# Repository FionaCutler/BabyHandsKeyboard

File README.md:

# Baby Hands Keyboard
A keyboard for those with smaller hands, layout designed by Brooke. Layout:

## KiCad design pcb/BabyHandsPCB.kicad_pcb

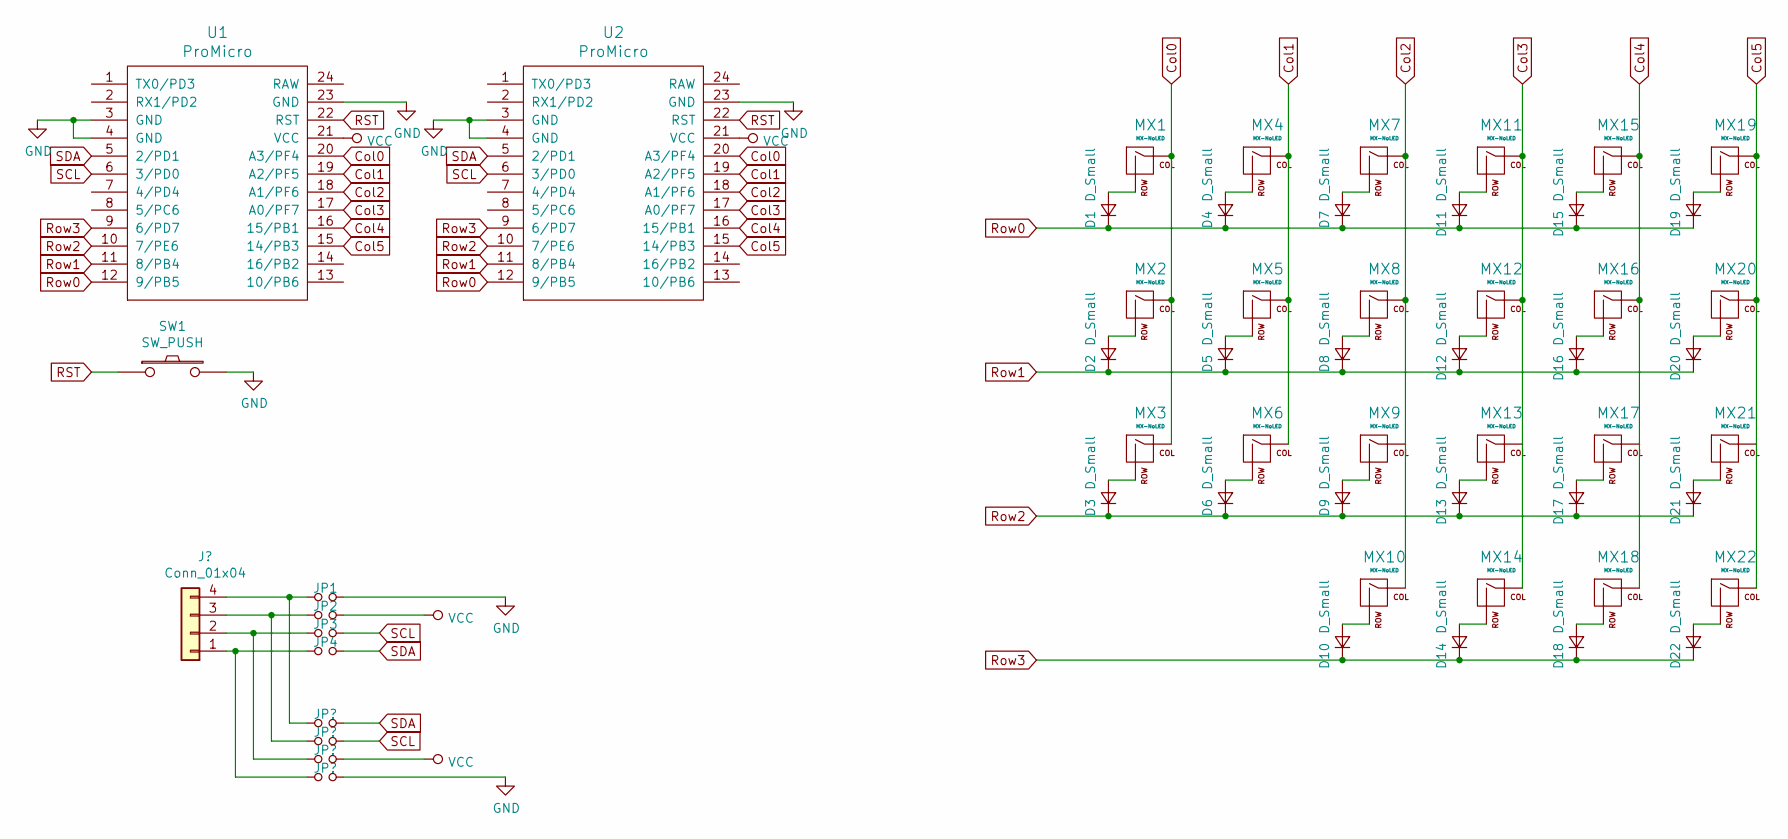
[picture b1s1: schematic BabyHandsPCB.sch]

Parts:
D1, D2, D3, D4, D5, D6, D7, D8, D9, D10, D11, D12, D13, D14, D15, D16, D17, D18, D19, D20, D21, D22: D_Small; D3_TH_SMD
JP1, JP2, JP3, JP4: Jumper_NO_Small; Jumper
MX1, MX2, MX3, MX4, MX5, MX6, MX7, MX8, MX9, MX10, MX11, MX12, MX13, MX14, MX15, MX16, MX17, MX19, MX20, MX21: MX-NoLED; CherryMX_Choc_Hotswap
MX18, MX22: MX-NoLED; CherryMX_Choc_Hotswap_1.5u
SW1: SW_PUSH; SW_Tactile_SPST_Angled_PTS645Vx31-2LFS
U1, U2: ProMicro; ArduinoProMicro-BackSide

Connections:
Col0: MX1.1 (COL), MX2.1 (COL), MX3.1 (COL), U1.20 (A3/PF4), U2.20 (A3/PF4)
Col1: MX4.1 (COL), MX5.1 (COL), MX6.1 (COL), U1.19 (A2/PF5), U2.19 (A2/PF5); also elsewhere on the board
Col2: MX7.1 (COL), MX8.1 (COL), MX9.1 (COL), MX10.1 (COL), U1.18 (A1/PF6), U2.18 (A1/PF6)
Col3: MX11.1 (COL), MX12.1 (COL), MX13.1 (COL), MX14.1 (COL), U1.17 (A0/PF7), U2.17 (A0/PF7)
Col4: MX15.1 (COL), MX16.1 (COL), MX17.1 (COL), MX18.1 (COL), U1.16 (15/PB1), U2.16 (15/PB1)
Col5: MX19.1 (COL), MX20.1 (COL), MX21.1 (COL), MX22.1 (COL), U1.15 (14/PB3), U2.15 (14/PB3)
GND: JP1.2, SW1.2, U1.3 (GND), U1.4 (GND), U1.23 (GND), U2.3 (GND), U2.4 (GND), U2.23 (GND); also elsewhere on the board
unnamed: D1.2 (A), MX1.2 (ROW)
unnamed: D2.2 (A), MX2.2 (ROW)
unnamed: D3.2 (A), MX3.2 (ROW)
unnamed: D4.2 (A), MX4.2 (ROW)
unnamed 11: D5.2 (A), MX5.2 (ROW); also elsewhere on the board
unnamed: D6.2 (A), MX6.2 (ROW)
unnamed: D7.2 (A), MX7.2 (ROW)
unnamed: D8.2 (A), MX8.2 (ROW)
unnamed: D9.2 (A), MX9.2 (ROW)
unnamed: D10.2 (A), MX10.2 (ROW)
unnamed: D11.2 (A), MX11.2 (ROW)
unnamed: D12.2 (A), MX12.2 (ROW)
unnamed: D13.2 (A), MX13.2 (ROW)
unnamed: D14.2 (A), MX14.2 (ROW)
unnamed: D15.2 (A), MX15.2 (ROW)
unnamed: D16.2 (A), MX16.2 (ROW)
unnamed: D17.2 (A), MX17.2 (ROW)
unnamed: D18.2 (A), MX18.2 (ROW)
unnamed: D19.2 (A), MX19.2 (ROW)
unnamed: D20.2 (A), MX20.2 (ROW)
unnamed: D21.2 (A), MX21.2 (ROW)
unnamed: D22.2 (A), MX22.2 (ROW)
unnamed 29: JP4.1; also elsewhere on the board
unnamed 30: JP3.1; also elsewhere on the board
unnamed 31: JP2.1; also elsewhere on the board
unnamed 32: JP1.1; also elsewhere on the board
RST: SW1.1, U1.22 (RST), U2.22 (RST)
Row0: D1.1 (K), D4.1 (K), D7.1 (K), D11.1 (K), D15.1 (K), D19.1 (K), U1.12 (9/PB5), U2.12 (9/PB5)
Row1: D2.1 (K), D5.1 (K), D8.1 (K), D12.1 (K), D16.1 (K), D20.1 (K), U1.11 (8/PB4), U2.11 (8/PB4)
Row2: D3.1 (K), D6.1 (K), D9.1 (K), D13.1 (K), D17.1 (K), D21.1 (K), U1.10 (7/PE6), U2.10 (7/PE6)
Row3: D10.1 (K), D14.1 (K), D18.1 (K), D22.1 (K), U1.9 (6/PD7), U2.9 (6/PD7)
SCL: JP3.2, U1.6 (3/PD0), U2.6 (3/PD0); also elsewhere on the board
SDA: JP4.2, U1.5 (2/PD1), U2.5 (2/PD1); also elsewhere on the board
VCC: JP2.2, U1.21 (VCC), U2.21 (VCC); also elsewhere on the board

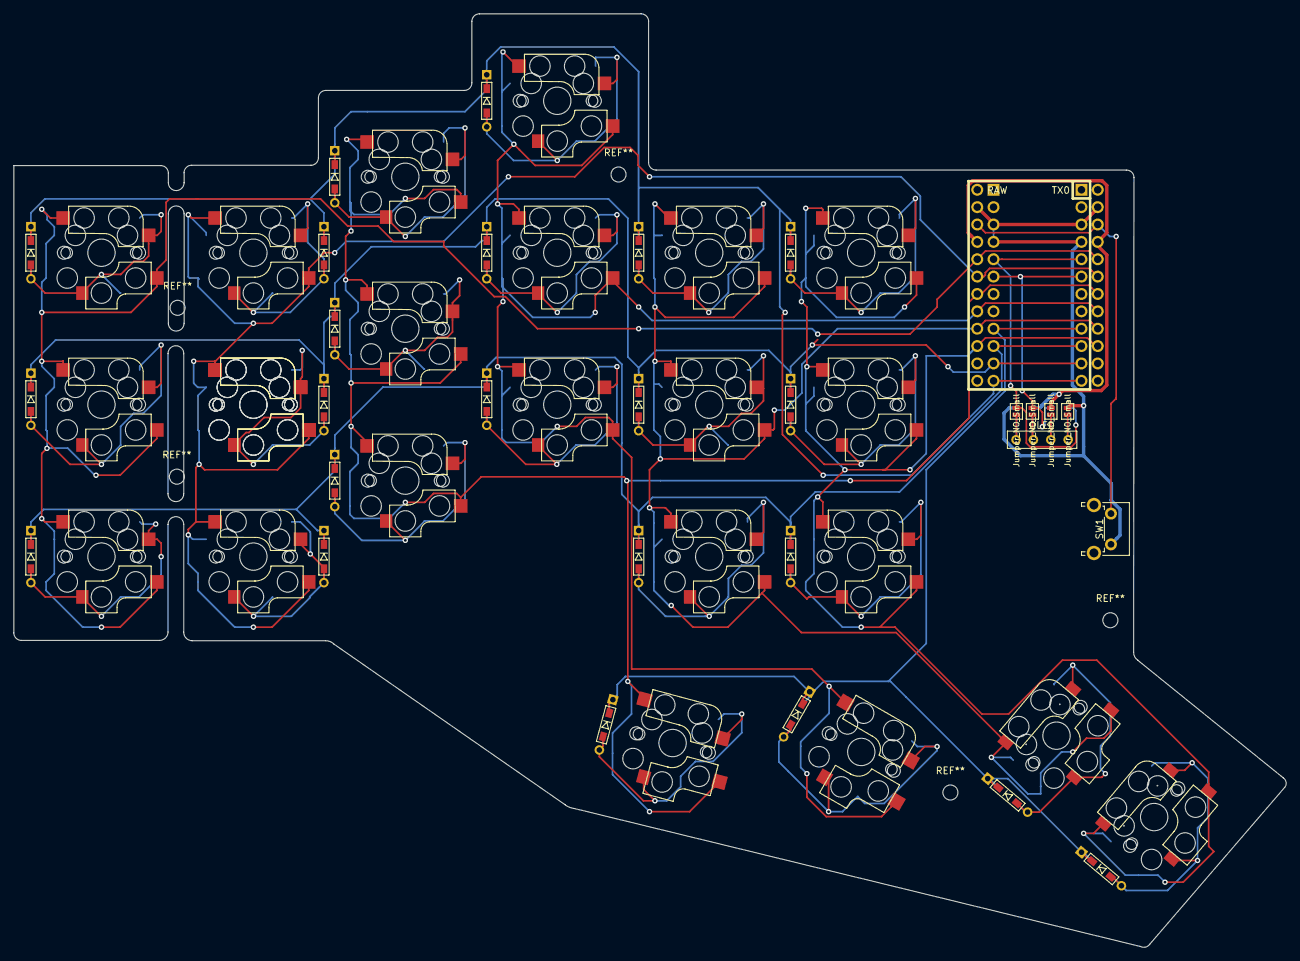
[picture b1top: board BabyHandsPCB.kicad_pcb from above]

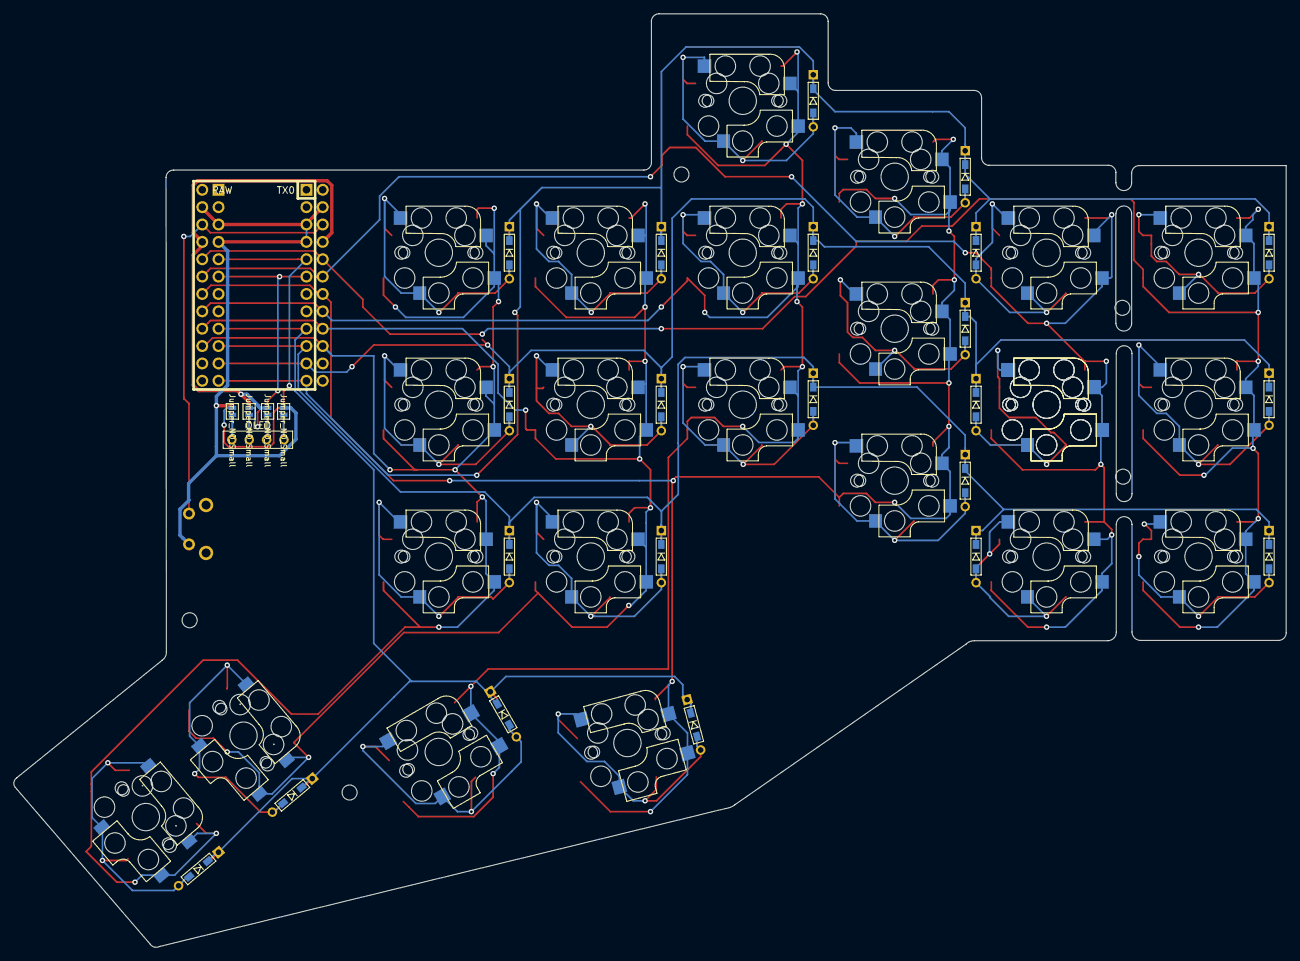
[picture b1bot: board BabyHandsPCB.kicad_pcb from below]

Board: 2 copper layers, 186.1 x 136.5 mm, 57 parts (5 on the bottom side), 41 nets.

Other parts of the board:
J1: Conn_01x04; OLED
JP5, JP6, JP7, JP8: Jumper_NO_Small; Jumper
MX5#2: MX-NoLED; CherryMX_Choc_Hotswap

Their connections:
Col1: MX5#2.1; also elsewhere on the board
GND: JP8.2; also elsewhere on the board
unnamed 11: MX5#2.2; also elsewhere on the board
unnamed 29: J1.1, JP8.1; also elsewhere on the board
unnamed 30: J1.2, JP7.1; also elsewhere on the board
unnamed 31: J1.3, JP6.1; also elsewhere on the board
unnamed 32: J1.4, JP5.1; also elsewhere on the board
SCL: JP6.2; also elsewhere on the board
SDA: JP5.2; also elsewhere on the board
VCC: JP7.2; also elsewhere on the board

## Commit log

2019-12-20 Create matrix schematic
2019-12-20 Place keys
2019-12-23 Route matrix
2019-12-24 Add pro micro
2019-12-31 Add outline
2019-12-31 Round edges
